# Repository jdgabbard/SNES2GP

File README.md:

# SNES2GP
A DIY adapter for using SNES controllers on vintage IBM PC Compatibles.

The SNES-2-GP was created for the exact purpose of bringing a good controller to the Vintage PC community. The truth is, I was playing Duke Nukem one day and thought,”This would be so much fun if I had a controller to play it with.” And then it hit me, I could create one that worked through the Gameport. At first, I decided that I would just hack a reproduction NES controller to work with the Gameport. However, this project only sent me down the rabbit hole of what would become one of the best projects I have completed yet.

Features include:<br><br>
-Two Working modes, determined by On/Off Switch.<br>
-Mode 1: Thrustmaster Compatible Mode.<br>
-Mode 2: 4-Axis Mode.<br>
-Two Primary Slots<br><br>

Disadvantages:<br><br>
-Appears to suffer from speed problems in some older DOS games. This causes the gamepad to not register movements in some cases.<br><br>

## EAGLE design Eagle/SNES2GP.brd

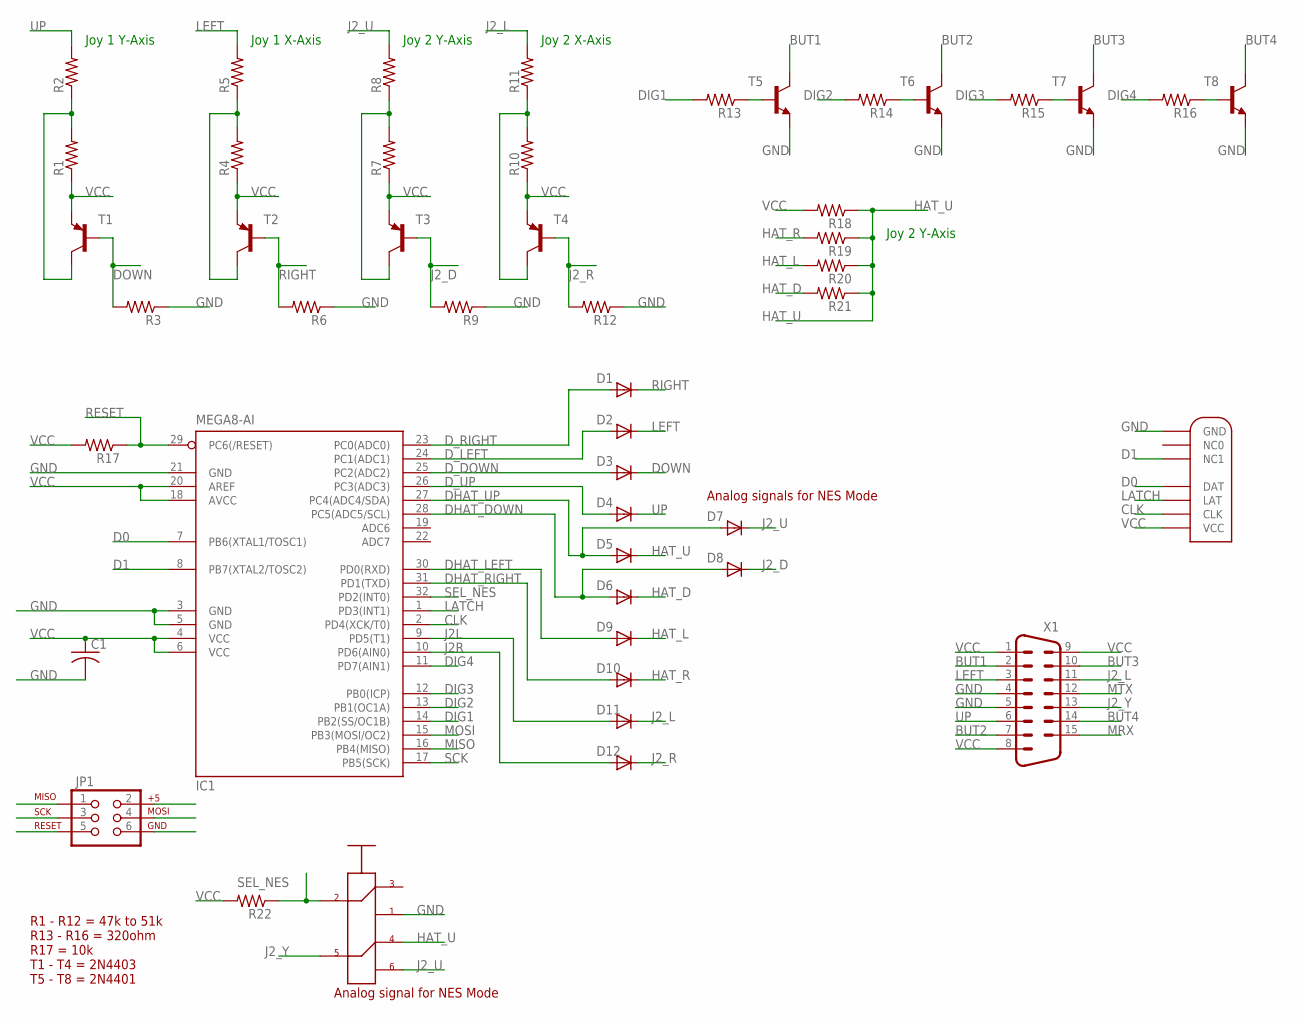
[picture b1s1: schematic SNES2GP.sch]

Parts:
C1: C-USC0805; C0805
D1, D2, D3, D4, D5, D6, D7, D8, D9, D10, D11, D12: DIODE-SOD323-W; SOD323-W
IC1: MEGA8-AI; TQFP32-08
JP1: AVR_SPI_PRG_6NS; 2X3-NS
R1, R2, R3, R4, R5, R6, R7, R8, R9, R10, R11, R12, R13, R14, R15, R16, R17, R18, R19, R20, R21, R22: R-US_M0805; M0805
T1, T2, T3, T4: MMBT3906; SOT23
T5, T6, T7, T8: MMBT3904; SOT23
U$1: 7X7_SW
U$3: SNES_GAMEPAD; SNESCONN
X1: M15HP

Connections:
BUT1: T5.3 (C), X1.2
BUT2: T6.3 (C), X1.7
BUT3: T7.3 (C), X1.10
BUT4: T8.3 (C), X1.14
CLK: IC1.2 (PD4(XCK/T0)), U$3.CLOCK (CLK)
D0: IC1.7 (PB6(XTAL1/TOSC1)), U$3.DATA (DAT)
D1: IC1.8 (PB7(XTAL2/TOSC2)), U$3.NC. (NC1)
DHAT_DOWN: D6.A, D8.A, IC1.28 (PC5(ADC5/SCL))
DHAT_LEFT: D9.A, IC1.30 (PD0(RXD))
DHAT_RIGHT: D10.A, IC1.31 (PD1(TXD))
DHAT_UP: D5.A, D7.A, IC1.27 (PC4(ADC4/SDA))
DIG1: IC1.14 (PB2(SS/OC1B)), R13.2
DIG2: IC1.13 (PB1(OC1A)), R14.2
DIG3: IC1.12 (PB0(ICP)), R15.2
DIG4: IC1.11 (PD7(AIN1)), R16.2
DOWN: D3.C, R3.2, T1.1 (B)
D_DOWN: D3.A, IC1.25 (PC2(ADC2))
D_LEFT: D2.A, IC1.24 (PC1(ADC1))
D_RIGHT: D1.A, IC1.23 (PC0(ADC0))
D_UP: D4.A, IC1.26 (PC3(ADC3))
GND: C1.2, IC1.3 (GND), IC1.5 (GND), IC1.21 (GND), JP1.6, R3.1, R6.1, R9.1, R12.1, T5.2 (E), T6.2 (E), T7.2 (E), T8.2 (E), U$1.P$1 (1), U$3.GND, X1.4, X1.5
HAT_D: D6.C, R21.2
HAT_L: D9.C, R20.2
HAT_R: D10.C, R19.2
HAT_U: D5.C, R18.1, R19.1, R20.1, R21.1, U$1.P$4 (4)
J2L: D11.A, IC1.9 (PD5(T1))
J2R: D12.A, IC1.10 (PD6(AIN0))
J2_D: D8.C, R9.2, T3.1 (B)
J2_L: D11.C, R11.2, X1.11
J2_R: D12.C, R12.2, T4.1 (B)
J2_U: D7.C, R8.2, U$1.P$6 (6)
J2_Y: U$1.P$5 (5), X1.13
LATCH: IC1.1 (PD3(INT1)), U$3.LATCH (LAT)
LEFT: D2.C, R5.2, X1.3
MISO: IC1.16 (PB4(MISO)), JP1.1
MOSI: IC1.15 (PB3(MOSI/OC2)), JP1.4
MRX: X1.15
MTX: X1.12
unnamed: R13.1, T5.1 (B)
unnamed: R1.2, R2.1, T1.3 (C)
unnamed: R14.1, T6.1 (B)
unnamed: R4.2, R5.1, T2.3 (C)
unnamed: R15.1, T7.1 (B)
unnamed: R7.2, R8.1, T3.3 (C)
unnamed: R16.1, T8.1 (B)
unnamed: R10.2, R11.1, T4.3 (C)
RESET: IC1.29 (PC6(/RESET)), JP1.5, R17.1
RIGHT: D1.C, R6.2, T2.1 (B)
SCK: IC1.17 (PB5(SCK)), JP1.3
SEL_NES: IC1.32 (PD2(INT0)), R22.1, U$1.P$2 (2)
UP: D4.C, R2.2, X1.6
VCC: C1.1, IC1.4 (VCC), IC1.6 (VCC), IC1.18 (AVCC), IC1.20 (AREF), JP1.2, R1.1, R4.1, R7.1, R10.1, R17.2, R18.2, R22.2, T1.2 (E), T2.2 (E), T3.2 (E), T4.2 (E), U$3.5V (VCC), X1.1, X1.8, X1.9

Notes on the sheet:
Joy 1 Y-Axis
Joy 1 X-Axis
R1 - R12 = 47k to 51k R13 - R16 = 320ohm R17 = 10k T1 - T4 = 2N4403 T5 - T8 = 2N4401
Joy 2 Y-Axis
Analog signals for NES Mode
Analog signal for NES Mode
Joy 2 X-Axis

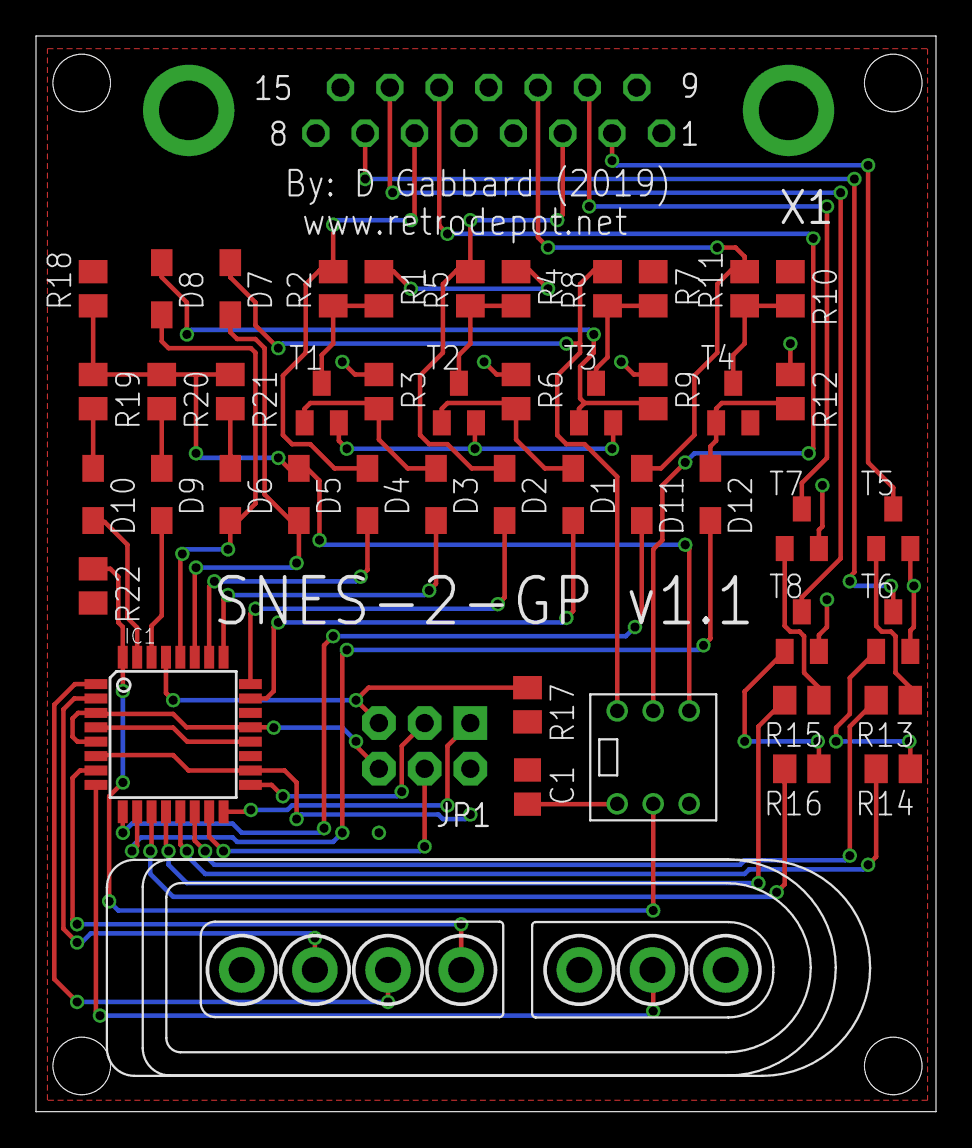
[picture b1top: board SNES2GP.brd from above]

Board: 2 copper layers, 50.0 x 59.8 mm, 48 parts (0 on the bottom side), 50 nets.

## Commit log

2022-09-09 Initial Upload
    Initial file upload.
2022-09-09 Create README.md
    Initial Readme upload.

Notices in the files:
parts and their libraries:
SparkFun-Connectors: Licensing: Creative Commons ShareAlike 4.0 International - https://creativecommons.org/licenses/by-sa/4.0
